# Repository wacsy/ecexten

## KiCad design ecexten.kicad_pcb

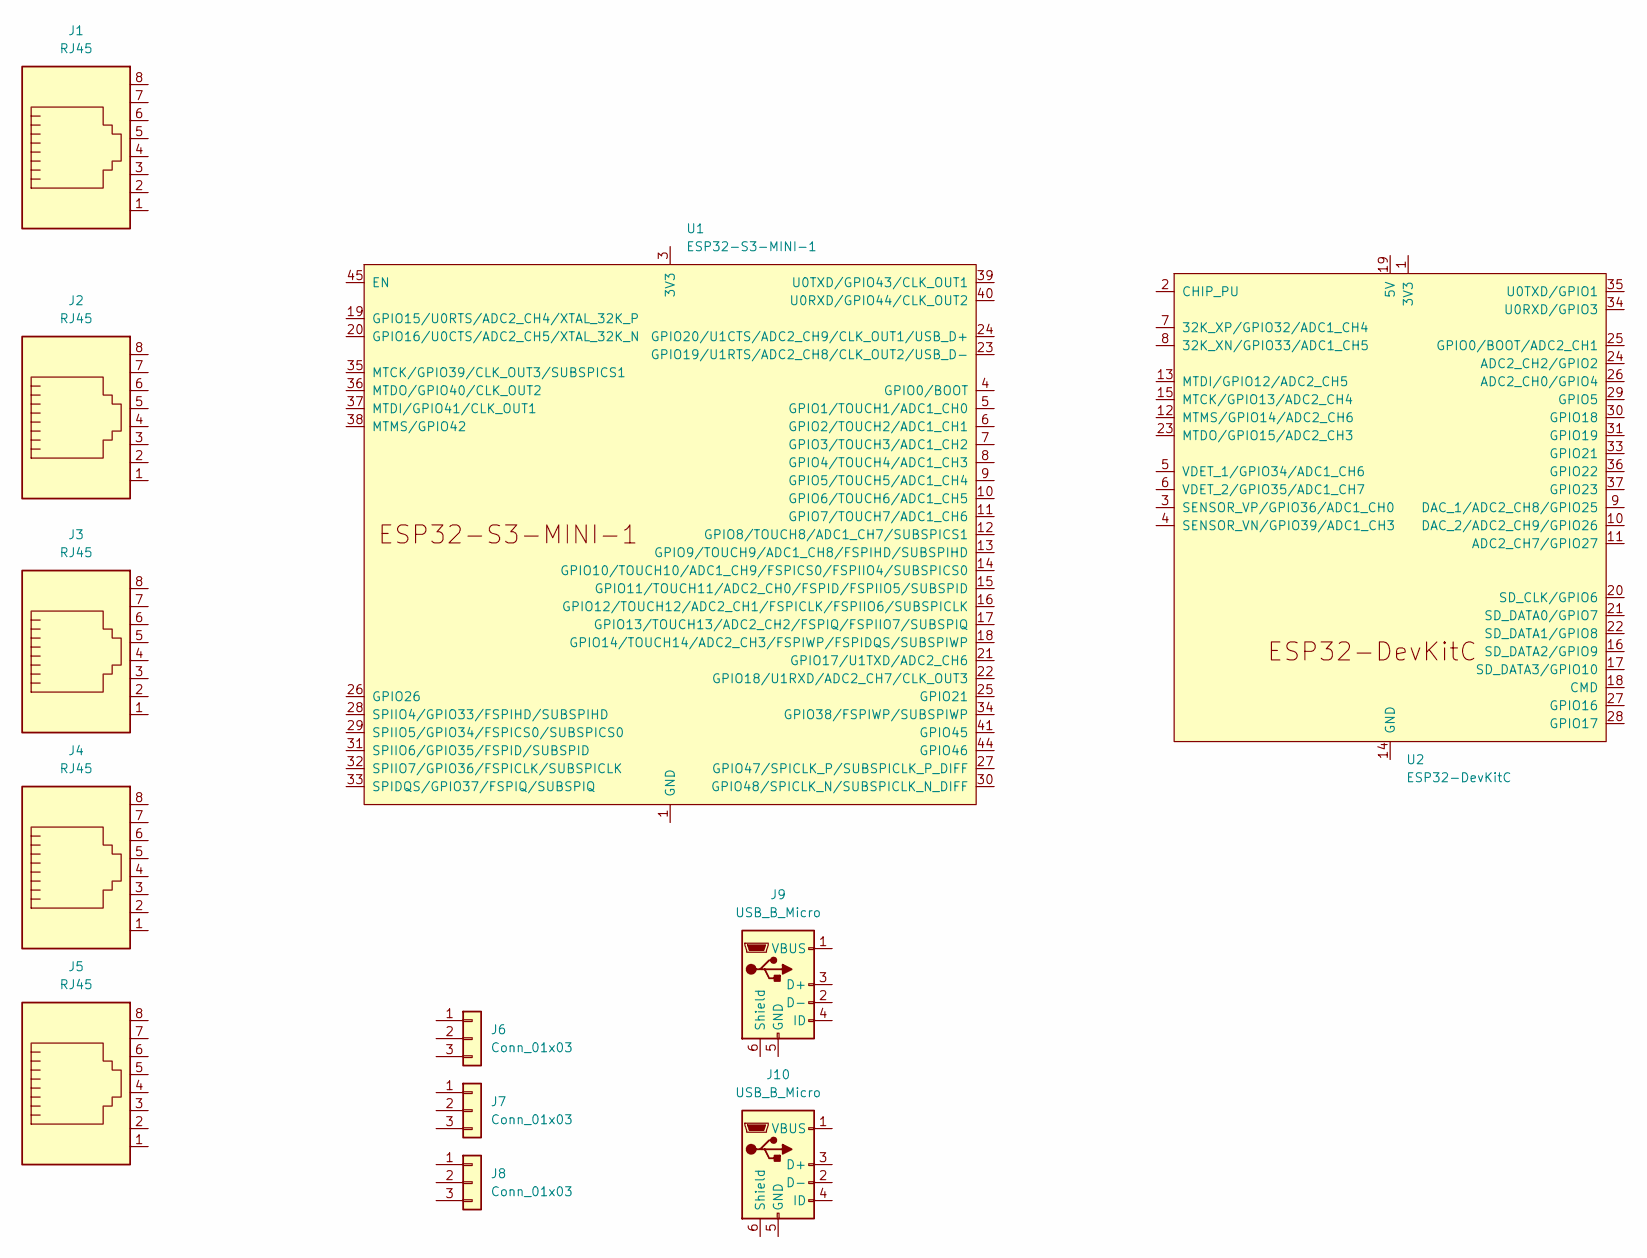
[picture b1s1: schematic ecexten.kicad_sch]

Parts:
J1, J2, J3, J4, J5: RJ45; RJ45_Amphenol_54602-x08_Horizontal
J6, J7, J8: Conn_01x03; PinHeader_1x03_P2.54mm_Vertical
J9, J10: USB_B_Micro; HRS_ZX62M-B-5P-4
U1: ESP32-S3-MINI-1
U2: ESP32-DevKitC

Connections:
unnamed: U1.1 (GND), U1.2 (GND), U1.42 (GND), U1.43 (GND), U1.46 (GND), U1.47 (GND), U1.48 (GND), U1.49 (GND), U1.50 (GND), U1.51 (GND), U1.52 (GND), U1.53 (GND), U1.54 (GND), U1.55 (GND), U1.56 (GND), U1.57 (GND), U1.58 (GND), U1.59 (GND), U1.60 (GND), U1.61 (GND), U1.62 (GND), U1.63 (GND), U1.64 (GND), U1.65 (GND)
unnamed: U2.14 (GND), U2.32 (GND), U2.38 (GND)

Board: 2 copper layers, 12 parts (0 on the bottom side), 2 nets, no tracks yet.

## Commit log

2023-09-26 init c
2023-09-26 add ignore and no backup
2023-09-26 add git ignore
2023-09-26 add libraries
